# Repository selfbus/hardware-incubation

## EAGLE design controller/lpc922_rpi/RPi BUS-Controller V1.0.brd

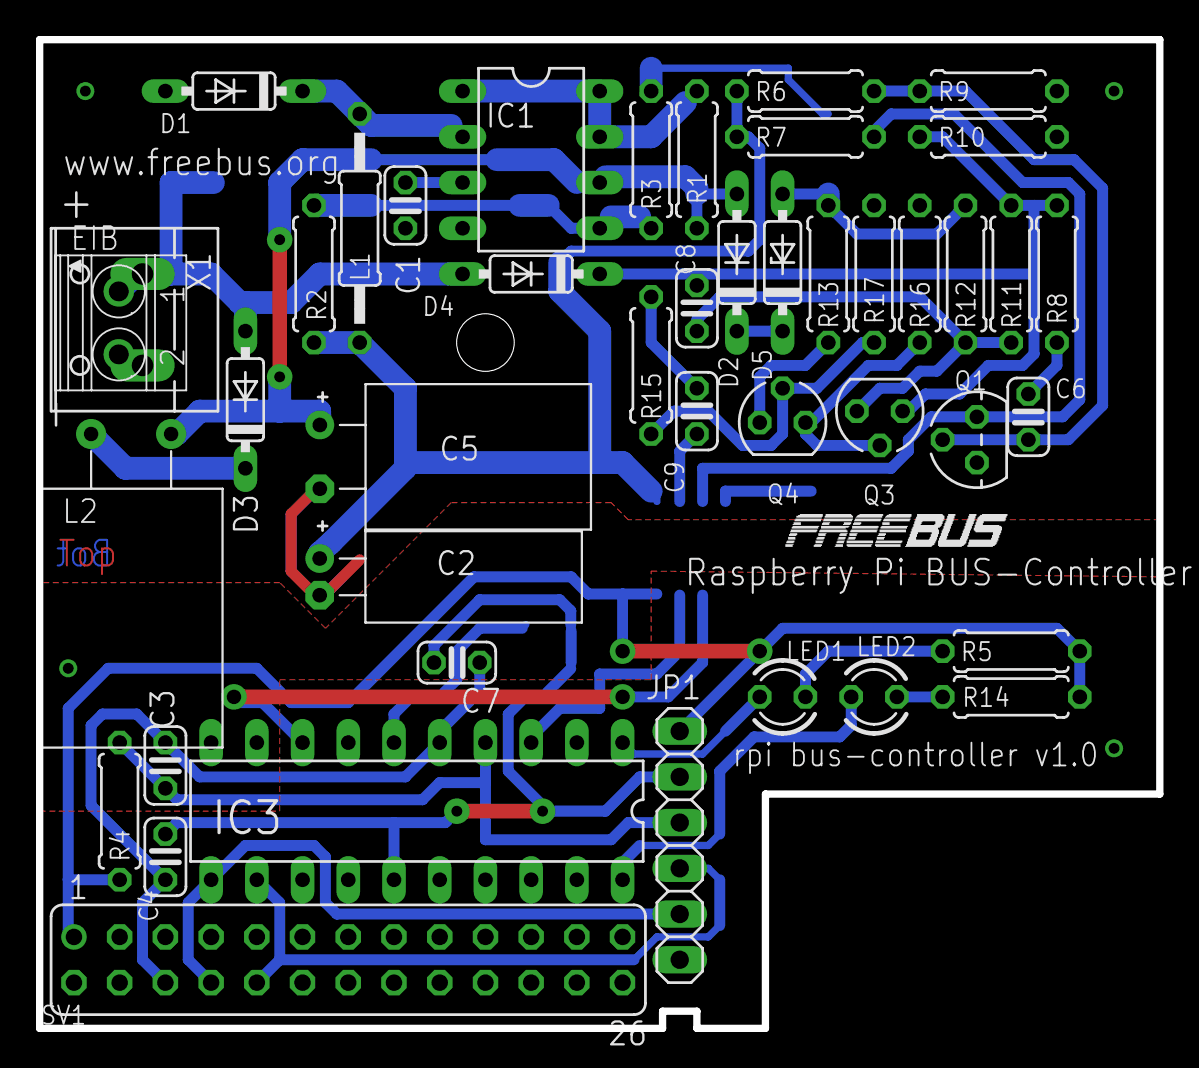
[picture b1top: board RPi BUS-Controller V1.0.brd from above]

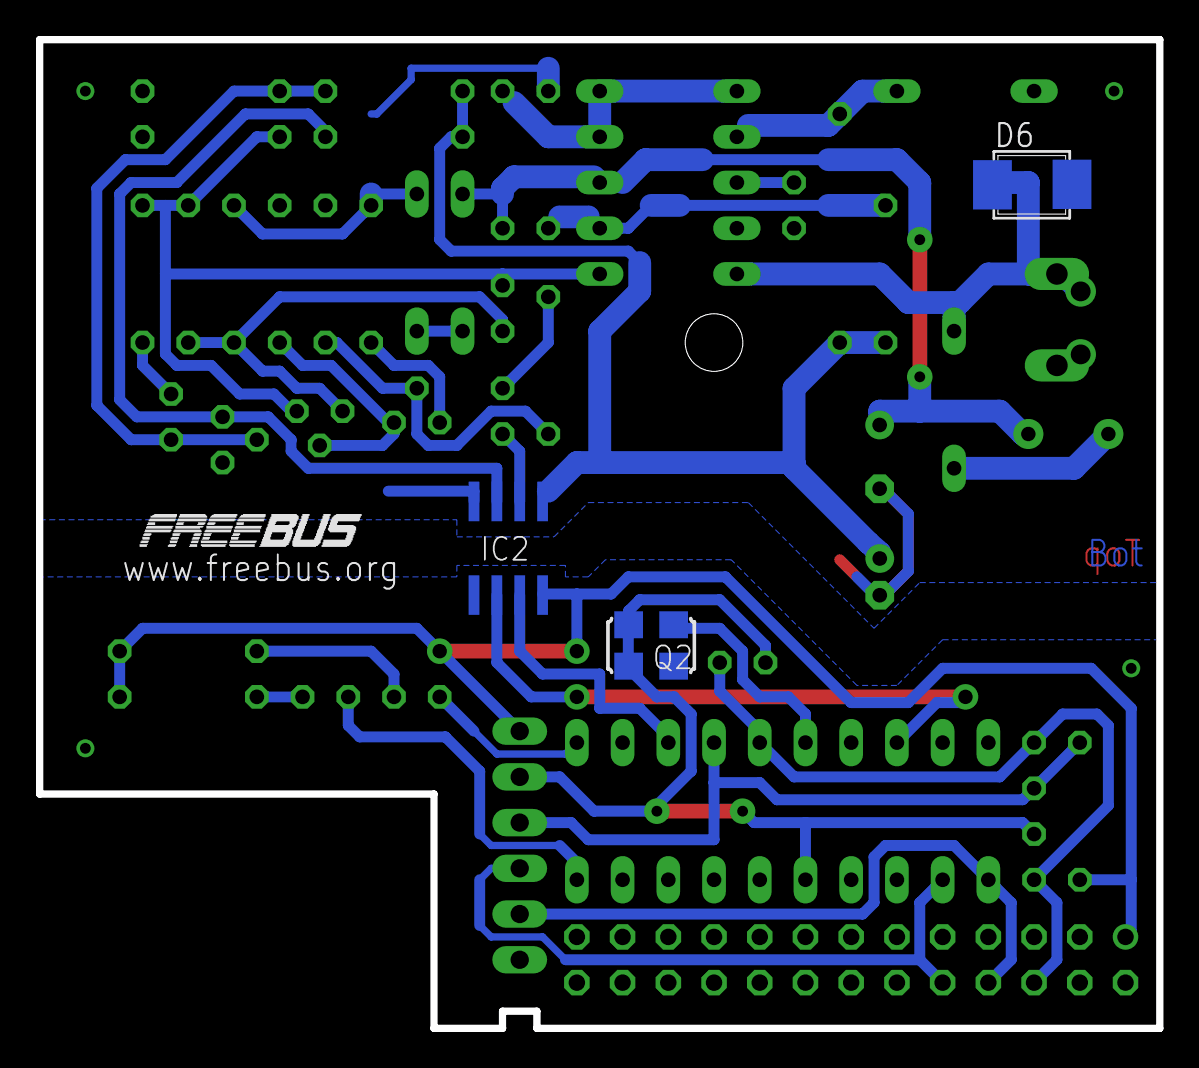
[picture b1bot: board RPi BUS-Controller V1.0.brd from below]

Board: 2 copper layers, 62.2 x 54.9 mm, 47 parts (3 on the bottom side), 34 nets.

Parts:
C1: 470p; C025-024X044
C2: 100µ; 2-5X11
C3, C4, C6: 100n; C025-024X044
C5: 100µ; 3,5-8X13
C7, C8, C9: 10n; C025-024X044
D1: BAT46; DO35-7
D2, D4: 4148; DO35-7
D3: 1N4148; DO35-7
D5: 7V5; DO35Z7
D6: SMAJ43CA; SMB
EIB: 1751248
IC1: MC34063AP; DIL08
IC2: ADUM1201; SO8
IC3: 89LPC922; DIL20
JP1: ISP; 1X06
L1: 220µ; 0207/12
L2: 150mH; RCL_11PH
LED1: rot; LED3MM
LED2: gruen; LED3MM
Q1: BC557; TO92
Q2: ASF1; ASF
Q3: BC640; SOT54D
Q4: BC547; SOT54A
R1: 3R3; 0207/7
R2: 3k6; 0207/7
R3, R11, R13: 2k2; 0207/7
R4: 4k7; 0207/7
R5, R12, R14: 1k; 0207/7
R6: 82k; 0207/7
R7, R8: 10k; 0207/7
R9: 47k; 0207/7
R10, R17: 100k; 0207/7
R15: 5k6; 0207/7
R16: 5R6; 0207/7
SV1: RPi Head; FE13-2
X1: BUS; W237-132

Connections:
/RESET: C3.2, IC3.4, JP1.3, R4.1
BASE: C6.2, Q1.2, R6.1, R9.2
EIB+: D3.A, D4.A, D6.1, EIB.1, X1.2
FETGATE: Q4.B, R15.2, R17.2
GND1: C1.2, C2.-, C5.-, D1.A, D6.2, EIB.2, IC1.4, IC2.4, Q1.3, R3.1, R9.1, R10.1, R16.1, R17.1, X1.1
GND2: C3.1, C4.1, C7.2, IC2.5, IC3.5, JP1.6, Q2.2, SV1.6
unnamed: Q4.C, R13.2
unnamed: IC2.3, Q1.1, R7.1
unnamed: IC3.6, Q2.3
unnamed: D2.C, D5.C
unnamed: IC2.7, IC3.3
unnamed: IC1.1, IC1.7, IC1.8, R1.1
unnamed: IC3.1, LED1.K
unnamed: IC1.5, R2.1, R3.2
unnamed: D1.C, IC1.2, L1.1
unnamed: D3.C, L2.P$2
unnamed: C1.1, IC1.3
unnamed: C6.1, R8.2
unnamed: C9.2, R15.1
unnamed: Q3.C, Q4.E, R16.2
unnamed: IC3.20, LED2.K
unnamed: C9.1, IC2.2
unnamed: LED2.A, R14.2
unnamed: D5.A, R12.1, R13.1
unnamed: C8.1, Q3.B, R11.2, R12.2
unnamed: IC3.12, JP1.4, SV1.10
unnamed: IC3.11, JP1.5, SV1.8
unnamed: LED1.A, R5.2
SIGIN: IC2.6, IC3.8
V+: C8.2, D4.C, Q3.E, R8.1, R10.2, R11.1
VCC: C4.2, C7.1, IC3.15, JP1.2, Q2.1, Q2.4
VDC: C5.+, D2.A, IC1.6, L2.P$1, R1.2
VDD1: C2.+, IC2.1, L1.2, R2.2, R6.2, R7.2
VDD2: IC2.8, JP1.1, R4.2, R5.1, R14.1, SV1.1

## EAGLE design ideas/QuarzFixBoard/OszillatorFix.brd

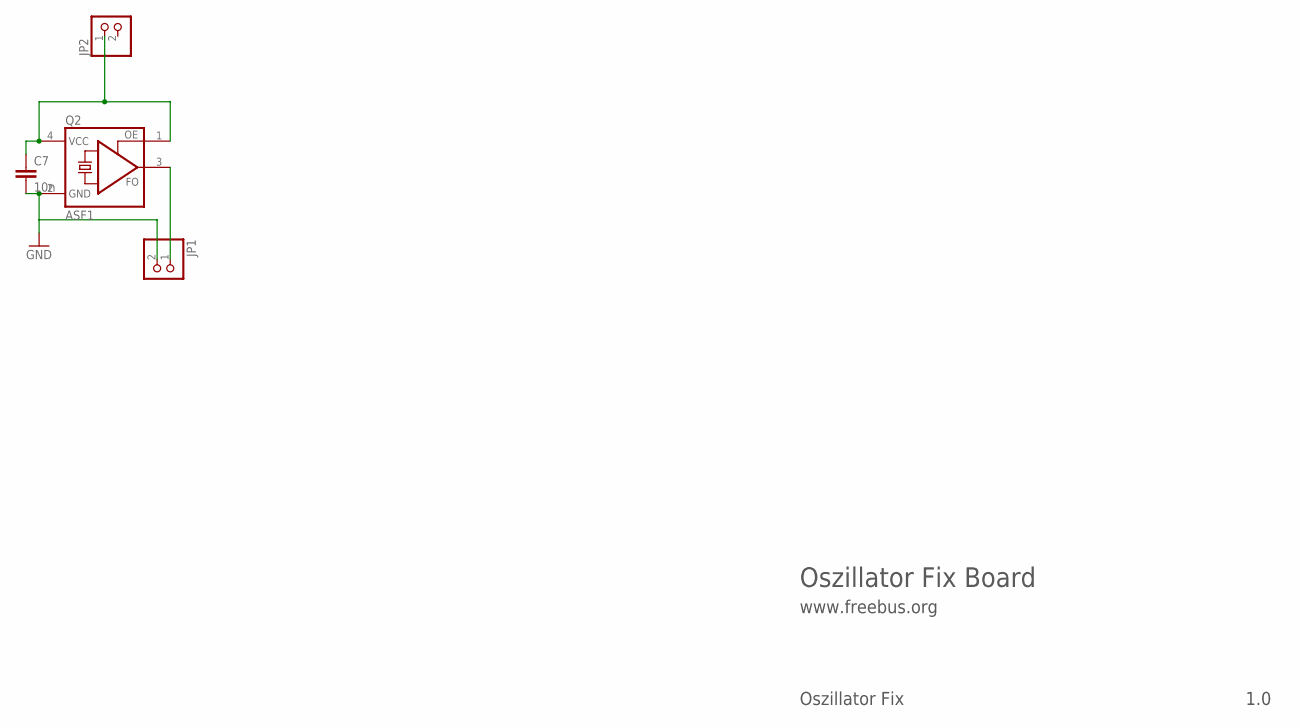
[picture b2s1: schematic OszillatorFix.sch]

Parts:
C7: 10n; C1206
JP1, JP2: PINHD-1X2; 1X02
Q2: ASF1; ASF

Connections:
GND2: C7.2, JP1.2, Q2.2 (GND)
unnamed: JP1.1, Q2.3 (FO)
VCC: C7.1, JP2.1, Q2.1 (OE), Q2.4 (VCC)

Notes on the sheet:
Oszillator Fix Board
www.freebus.org
Oszillator Fix
1.0

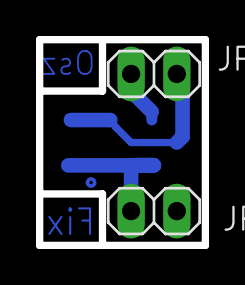
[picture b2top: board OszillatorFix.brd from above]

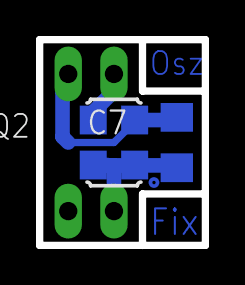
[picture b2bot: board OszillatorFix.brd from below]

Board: 2 copper layers, 9.2 x 11.4 mm, 4 parts (2 on the bottom side), 3 nets.
